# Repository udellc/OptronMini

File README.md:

# OptronMini
Repo for the Optron Mini

# Project Wiki:
https://github.com/udellc/OptronMini/wiki

# Folder Details
### BOM
Link to live spreadsheet of materials and links to products
### CAD
DXF: Laser Cutting File for Mini Frame
PCB: .sch and .brd files for Mini Circuit board
STL: 3D printer files
Archive: Old file dump for your enjoyment
### Code
Arduino code to download onto your Adafruit ItsyBitsy M4
### MaxMSP
Max8 apps tto use your Optron Mini!

# Getting Started
Please visit the Optron Project Wiki for setting up your Optron Mini!

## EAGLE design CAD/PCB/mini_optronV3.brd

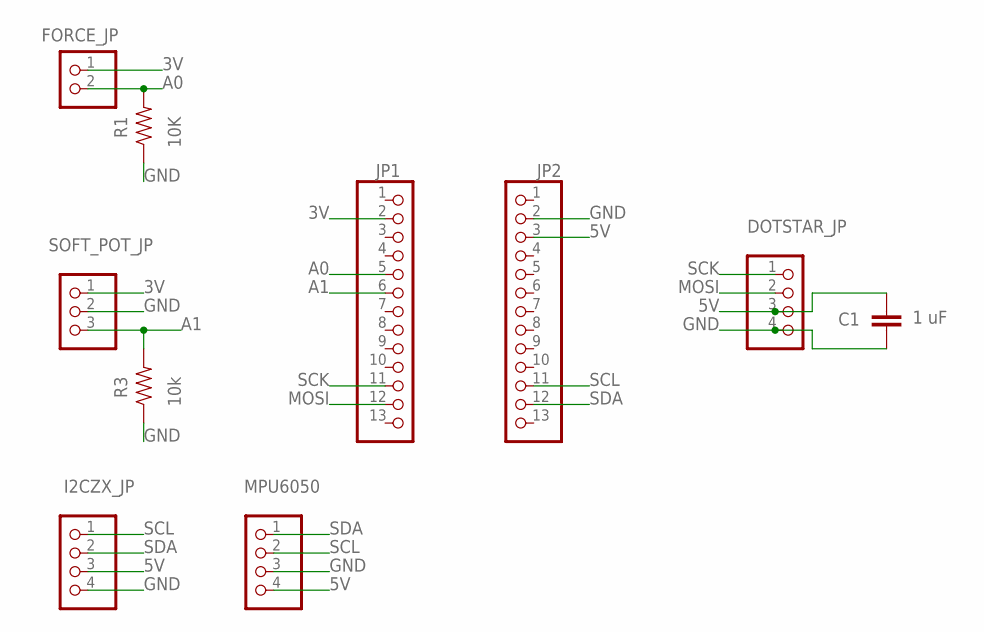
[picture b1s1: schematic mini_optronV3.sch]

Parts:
C1: 1 uF; C5B7.2; MPN 0805YD105KAT2A
DOTSTAR_JP: PINHD-1X4; 1X04
FORCE_JP: PINHD-1X2; 1X02
I2CZX_JP: PINHD-1X4; 1X04
JP1, JP2: PINHD-1X13_BIG; 1X13-BIG
MPU6050: PINHD-1X4; 1X04
R1: 10K; AXIAL-0.3; MPN CRCW060310K0FKEA
R3: 10k; AXIAL-0.3; MPN CRCW060310K0FKEA
SOFT_POT_JP: PINHD-1X3; 1X03

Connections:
3V: FORCE_JP.1, JP1.2, SOFT_POT_JP.1
5V: C1.1, DOTSTAR_JP.3, I2CZX_JP.3, JP2.3, MPU6050.4
A0: FORCE_JP.2, JP1.5, R1.P$2 (2)
A1: JP1.6, R3.P$2 (2), SOFT_POT_JP.3
GND: C1.2, DOTSTAR_JP.4, I2CZX_JP.4, JP2.2, MPU6050.3, R1.P$1 (1), R3.P$1 (1), SOFT_POT_JP.2
MOSI: DOTSTAR_JP.2, JP1.12
SCK: DOTSTAR_JP.1, JP1.11
SCL: I2CZX_JP.1, JP2.11, MPU6050.2
SDA: I2CZX_JP.2, JP2.12, MPU6050.1

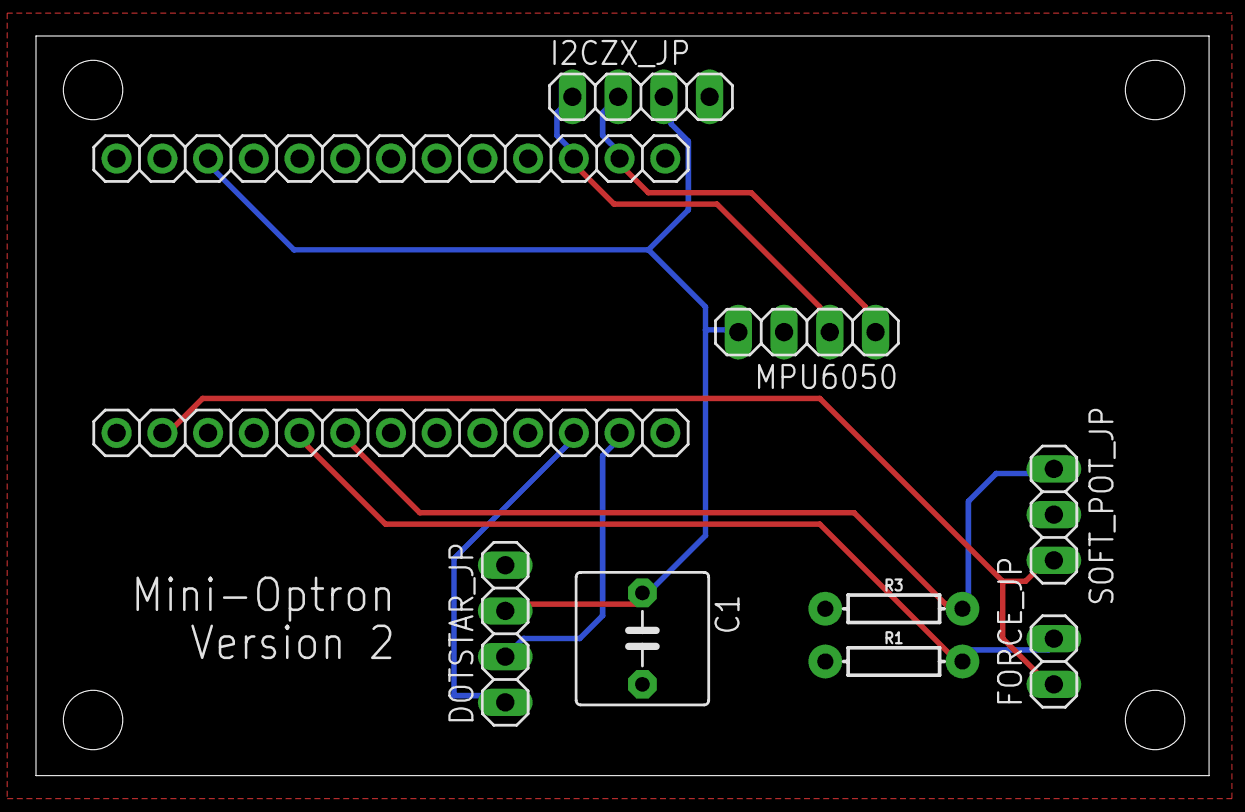
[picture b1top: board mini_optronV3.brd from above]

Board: 2 copper layers, 65.2 x 41.1 mm, 10 parts (0 on the bottom side), 9 nets.

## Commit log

2020-05-01 Create dependencies
2020-05-07 Add files via upload
    Mini-optron schematic and board layout.
2020-05-07 Updated FSR circuit, c1 orient
2020-07-09 UpdateMaxMSP07.09.20
2020-08-08 MaxPatches Sensors LEDs
2020-08-08 add BOM folder
2020-08-09 Major Max Mini Patch release 1.0
2020-08-25 Update Loom and MPG folders
2020-08-27 OptronUpgrade
2020-08-27 Large optron updatemax
2020-09-04 ds store
2020-09-15 Optron Mini App fix
2020-10-06 UpdateDesignFilesCadPcb
2020-10-06 UpdateMax
2020-10-20 add libraries arduino
2020-10-20 Add ZX library
2020-11-03 Add crystal vst and ambisonics
2020-12-10 update dependencies
2020-12-11 Update library and projects
2020-12-15 Add Giphy install photos
2020-12-15 add giphy installation
2021-10-07 update patterns
2022-01-26 upload arduino code
2022-06-07 Update LEDs and ZX sensor

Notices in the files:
parts and their libraries:
SparkFun-Resistors: Licensing: Creative Commons ShareAlike 4.0 International - https://creativecommons.org/licenses/by-sa/4.0
